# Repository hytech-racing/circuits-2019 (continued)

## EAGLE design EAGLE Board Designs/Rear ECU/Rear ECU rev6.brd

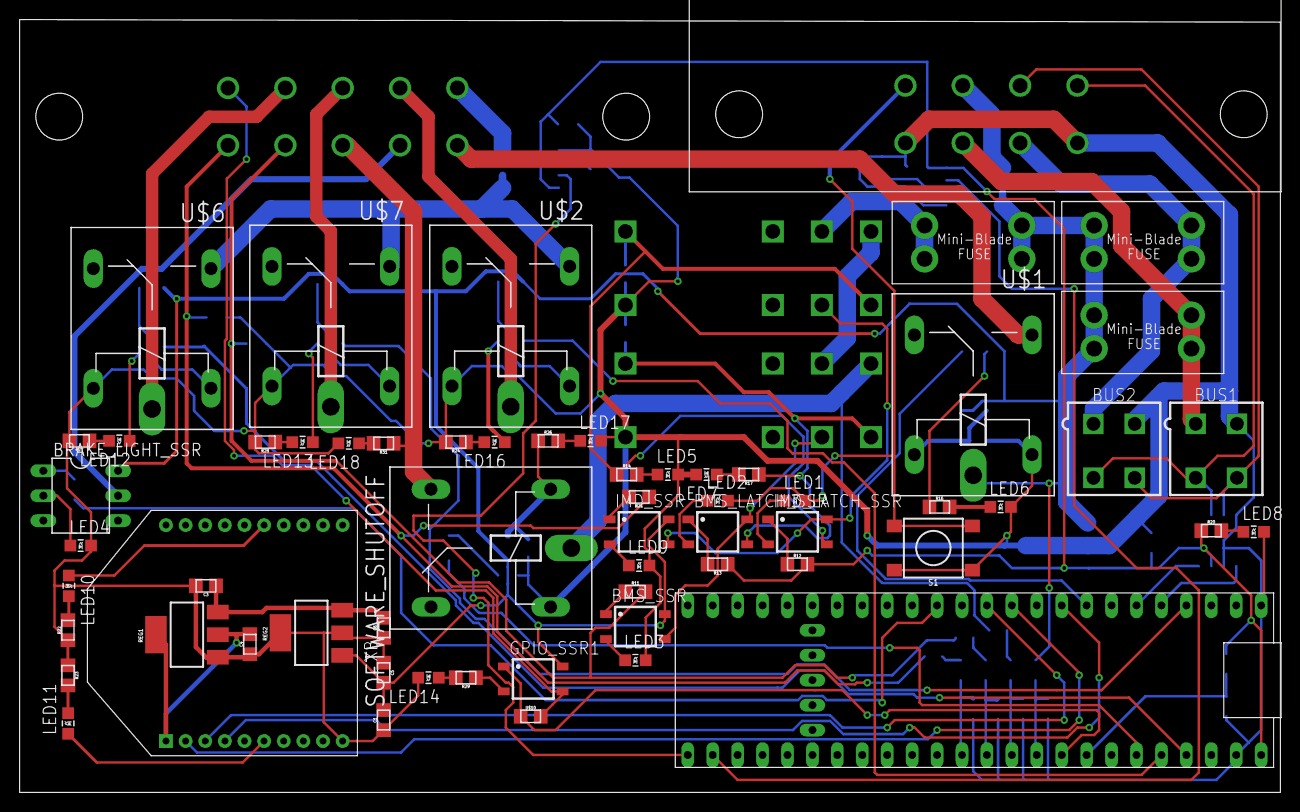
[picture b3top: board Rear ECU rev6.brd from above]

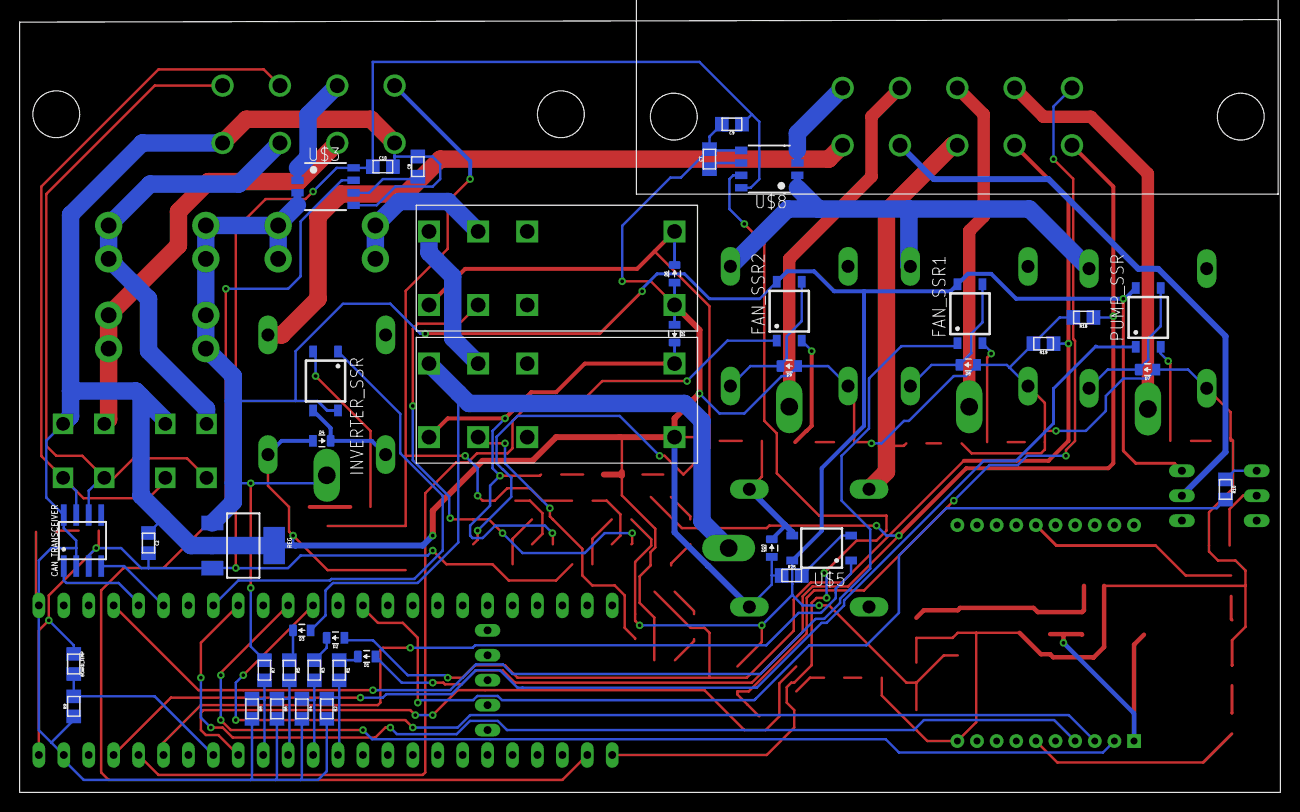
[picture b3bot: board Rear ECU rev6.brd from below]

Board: 2 copper layers, 128.4 x 78.7 mm, 102 parts (41 on the bottom side), 88 nets.

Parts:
BMS_LATCH_SSR: CPC1002N; SOP04
BMS_SSR: CPC1002N; SOP04
BOARD_TEMP: THERMISTOR_NCP210805; 0805
BRAKE_LIGHT_SSR: SOLID_STATE_RELAY_VO14642AT; DIL06
BUS1, BUS2: CONNECTOR-4; MINIFIT_5566-4
C1, C5: .22uF; 0805
C2, C6: .1uF; 0805
C3, C4: 1uF; 0805
C7, C8, C9, C10: 0805
CAN_TRANSCEIVER: MCP2551; SOIC-08
D1, D2, D3, D4, D5, D6, D7, D8, D9, D10: DIODE0805; 0805_D
FAN_SSR1, FAN_SSR2: CPC1002N; SOP04
FUSE_BUS_1, FUSE_BUS_2: 5A; MINI-BLADE_FUSE_HOLDER
GPIO_SSR1: CPC1002N; SOP04
IMD_LATCH_SSR: CPC1002N; SOP04
IMD_SHUTDOWN, IMD_SHUTDOWN1: G2RL-2-DC12; G2RL-2
IMD_SSR: CPC1002N; SOP04
INVERTER_SSR: CPC1002N; SOP04
LED1, LED2: White; LED-805
LED3, LED7, LED11: Green; LED-805
LED4, LED6, LED10, LED12, LED13, LED14, LED16: Red; LED-805
LED5, LED9: Yellow; LED-805
LED8: Purple; LED-805
LED17, LED18: RED; LED-805
PUMP_SSR: CPC1002N; SOP04
R1, R3, R5, R7: 43k; 0805
R2, R4, R6, R8: 12k; 0805
R9, R19: 10k; 0805
R10, R11, R16, R29: 43; 0805
R12, R13, R23, R24, R27, R28: 33; 0805
R14, R17, R21: 820; 0805
R18: 2.2k; 0805
R20: 270; 0805
R22: 100; 0805
R25: 330; 0805
R26, R31: 1.2K; 0805
REG, REG2: 5V; SOT223
REG1: TLV1117LV33; SOT223
S1: TACTILE_SWITCH_SMD_6.2MM_TALL
SHUTDWN_FUSE: 5A; MINI-BLADE_FUSE_HOLDER
SOFTWARE_SHUTOFF: G5LE; ZF112
U$1, U$2, U$6, U$7: G5LE; ZF112
U$3, U$8: ACS715_CURRENT_SENSOR; SOP8
U$4: TEENSY_3.5_EXT
U$5: CPC1002N; SOP04
U$10: JUMPER; 0805
X1: CONNECTOR-8MX150L_RIGHT_ANGLE-8; MX150L_RIGHT_ANGLE-8
X3: CONNECTOR-10MX150L-RIGHT_ANGLE-10; MX150L_RIGHT_ANGLE-10
XB: XBEE

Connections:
12VIN: U$3.1, U$3.2, X1.7
12VSUPPLY_READ: R7.2, R8.1, U$4.A3
12V_F1: BUS1.1, FUSE_BUS_1.R1, FUSE_BUS_1.R2, X1.3
12V_F2: BUS2.1, FUSE_BUS_2.R1, FUSE_BUS_2.R2, X1.2
+5V: BOARD_TEMP.1, C2.2, C9.1, C10.1, CAN_TRANSCEIVER.3, R12.2, R13.1, R20.1, REG.3, U$3.8, U$4.VIN, U$8.8
+12V: BMS_SSR.4, BRAKE_LIGHT_SSR.6, C1.2, C5.2, FAN_SSR1.4, FAN_SSR2.4, FUSE_BUS_1.L1, FUSE_BUS_1.L2, FUSE_BUS_2.L1, FUSE_BUS_2.L2, GPIO_SSR1.4, IMD_SSR.4, INVERTER_SSR.4, PUMP_SSR.4, R7.1, REG.1, REG2.1, SHUTDWN_FUSE.R1, SHUTDWN_FUSE.R2, U$1.P, U$3.3, U$3.4, U$5.4
BMS_COIL_PWR: BMS_LATCH_SSR.3, D5.C, IMD_SHUTDOWN1.4, IMD_SHUTDOWN1.COIL-, R17.1
BMS_OK: D2.A, R11.2, R19.1, X3.2
BMS_OK_READ: R3.2, R4.1, U$4.A1
BMS_PWR_STEP: BMS_LATCH_SSR.4, BMS_SSR.3, IMD_SHUTDOWN1.3
BRAKE_LIGHT: BRAKE_LIGHT_SSR.5, X3.4
BRAKE_LIGHT_CTRL: R10.2, U$4.D12
CANH: BUS1.4, BUS2.4, CAN_TRANSCEIVER.7, X1.6
CANL: BUS1.3, BUS2.3, CAN_TRANSCEIVER.6, X1.5
COOLCURRENTSIGNAL: U$4.A14, U$8.7
CURRENTSENSE2: U$2.S, U$6.S, U$7.S, U$8.1, U$8.2
ECUCURRENTSIGNAL: U$3.7, U$4.A15
FAN1-: U$7.P, X3.8
FAN2-: U$2.P, X3.9
GND: BUS1.2, BUS2.2, C1.1, C2.1, C3.2, C4.1, C5.1, C6.1, C7.2, C8.2, C9.2, C10.2, CAN_TRANSCEIVER.2, CAN_TRANSCEIVER.8, D4.A, D5.A, D6.A, D7.A, D8.A, D9.A, D10.A, IMD_SHUTDOWN.COIL+, IMD_SHUTDOWN1.COIL+, LED3.C, LED4.C, LED5.C, LED6.C, LED7.C, LED8.C, LED9.C, LED14.C, LED17.C, LED18.C, R2.2, R4.2, R6.2, R8.2, R9.1, R18.2, R19.2, R22.1, R23.1, R24.2, R25.1, R27.2, R28.2, REG.2, REG.4, REG1.1, REG2.2, REG2.4, S1.B1, S1.B2, SOFTWARE_SHUTOFF.1, U$1.2, U$2.1, U$3.5, U$4.AGND, U$4.GND, U$6.1, U$7.1, U$8.5, X1.1, X1.4, XB.10
GND1: U$8.3, U$8.4, X3.10
GPIO_1: GPIO_SSR1.3, U$10.2, X3.6
GPIO_CTRL1: GPIO_SSR1.1, U$4.A4, U$10.1
IMD_COIL_PWR: D6.C, IMD_LATCH_SSR.3, IMD_SHUTDOWN.4, IMD_SHUTDOWN.COIL-, R14.1
IMD_PWR_STEP: IMD_LATCH_SSR.4, IMD_SHUTDOWN.3, IMD_SSR.3
INVERTER_CTRL: INVERTER_SSR.1, U$4.D6
INVERTER_SUPPLY: U$1.S, X3.5
LATCH_EXT_BUTTON: LED1.C, LED2.C, S1.A1, S1.A2, X1.8
unnamed: IMD_LATCH_SSR.2, LED1.A
unnamed: CAN_TRANSCEIVER.4, U$4.D4(CANRX)
unnamed: CAN_TRANSCEIVER.1, U$4.D3(CANTX)
unnamed: D7.C, PUMP_SSR.3, U$6.2
unnamed: IMD_LATCH_SSR.1, R12.1
unnamed: GPIO_SSR1.2, R29.1
unnamed: BRAKE_LIGHT_SSR.2, LED4.A
unnamed: BMS_SSR.2, LED3.A
unnamed: LED10.A, XB.15
unnamed: LED10.C, R22.2
unnamed: BMS_LATCH_SSR.1, R13.2
unnamed: LED14.A, R29.2
unnamed: BOARD_TEMP.2, R9.2, U$4.A5
unnamed: BMS_LATCH_SSR.2, LED2.A
unnamed: BRAKE_LIGHT_SSR.1, R10.1
unnamed: BMS_SSR.1, R11.1
unnamed: LED5.A, R14.2
unnamed: D8.C, FAN_SSR1.3, U$7.2
unnamed: D9.C, FAN_SSR2.3, U$2.2
unnamed: D1.C, R1.1
unnamed: D2.C, R3.1
unnamed: D3.C, R5.1
unnamed: LED11.A, XB.6
unnamed: D4.C, INVERTER_SSR.3, U$1.1
unnamed: INVERTER_SSR.2, R16.1
unnamed: LED6.A, R16.2
unnamed: LED8.A, R20.2
unnamed: LED16.C, R24.1
unnamed: IMD_SSR.1, R21.2
unnamed: LED7.A, R17.2
unnamed: LED11.C, R23.2
unnamed: IMD_SSR.2, LED9.A
unnamed: C3.1, C6.2, REG1.3, REG2.3
unnamed: LED13.C, R28.1
unnamed: LED12.C, R27.1
unnamed: LED12.A, PUMP_SSR.2
unnamed: FAN_SSR2.2, LED16.A
unnamed: LED18.A, R31.2
unnamed: FAN_SSR1.2, LED13.A
unnamed: D10.C, R26.1, SOFTWARE_SHUTOFF.2, U$5.3
unnamed: R25.2, U$5.2
unnamed: LED17.A, R26.2
unnamed: C7.1, U$8.6
unnamed: C8.1, U$3.6
OKHS: D1.A, R18.1, R21.1, X3.1
OKHS_READ: R1.2, R2.1, U$4.A0
PUMP1-: U$6.P, X3.7
RELAY_CTRL1: PUMP_SSR.1, U$4.A9
RELAY_CTRL2: FAN_SSR1.1, U$4.D2
RELAY_CTRL3: FAN_SSR2.1, U$4.A8
SHUTDOWN_A: IMD_SHUTDOWN.6, SHUTDWN_FUSE.L1, SHUTDWN_FUSE.L2
SHUTDOWN_B: IMD_SHUTDOWN.5, IMD_SHUTDOWN1.6
SHUTDOWN_C: D3.A, IMD_SHUTDOWN1.5, SOFTWARE_SHUTOFF.P
SHUTDOWN_D: R31.1, SOFTWARE_SHUTOFF.S, X3.3
SHUTDOWN_OUT_READ: R5.2, R6.1, U$4.A2
SOFTWARE_SHUTDOWN: U$4.A7, U$5.1
VCC: C4.2, REG1.2, REG1.4, XB.1
XB8: U$4.D7(RX3), XB.4
XBDI: U$4.D10(TX2), XB.3
XBDO: U$4.D9(RX2), XB.2
